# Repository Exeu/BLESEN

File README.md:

# BLESEN
## Bluetooth Low Energy - Sensor 

A simple playground for testing and developing BLE devices.

This Design has a built in 2.4 Ghz 50 Ohm PCB Antennna and is featuring two different sesnsors.

More to come.

## Schematic
[Schematic](BLESEN-Schematic.pdf)

## PCB

## Early prototypes

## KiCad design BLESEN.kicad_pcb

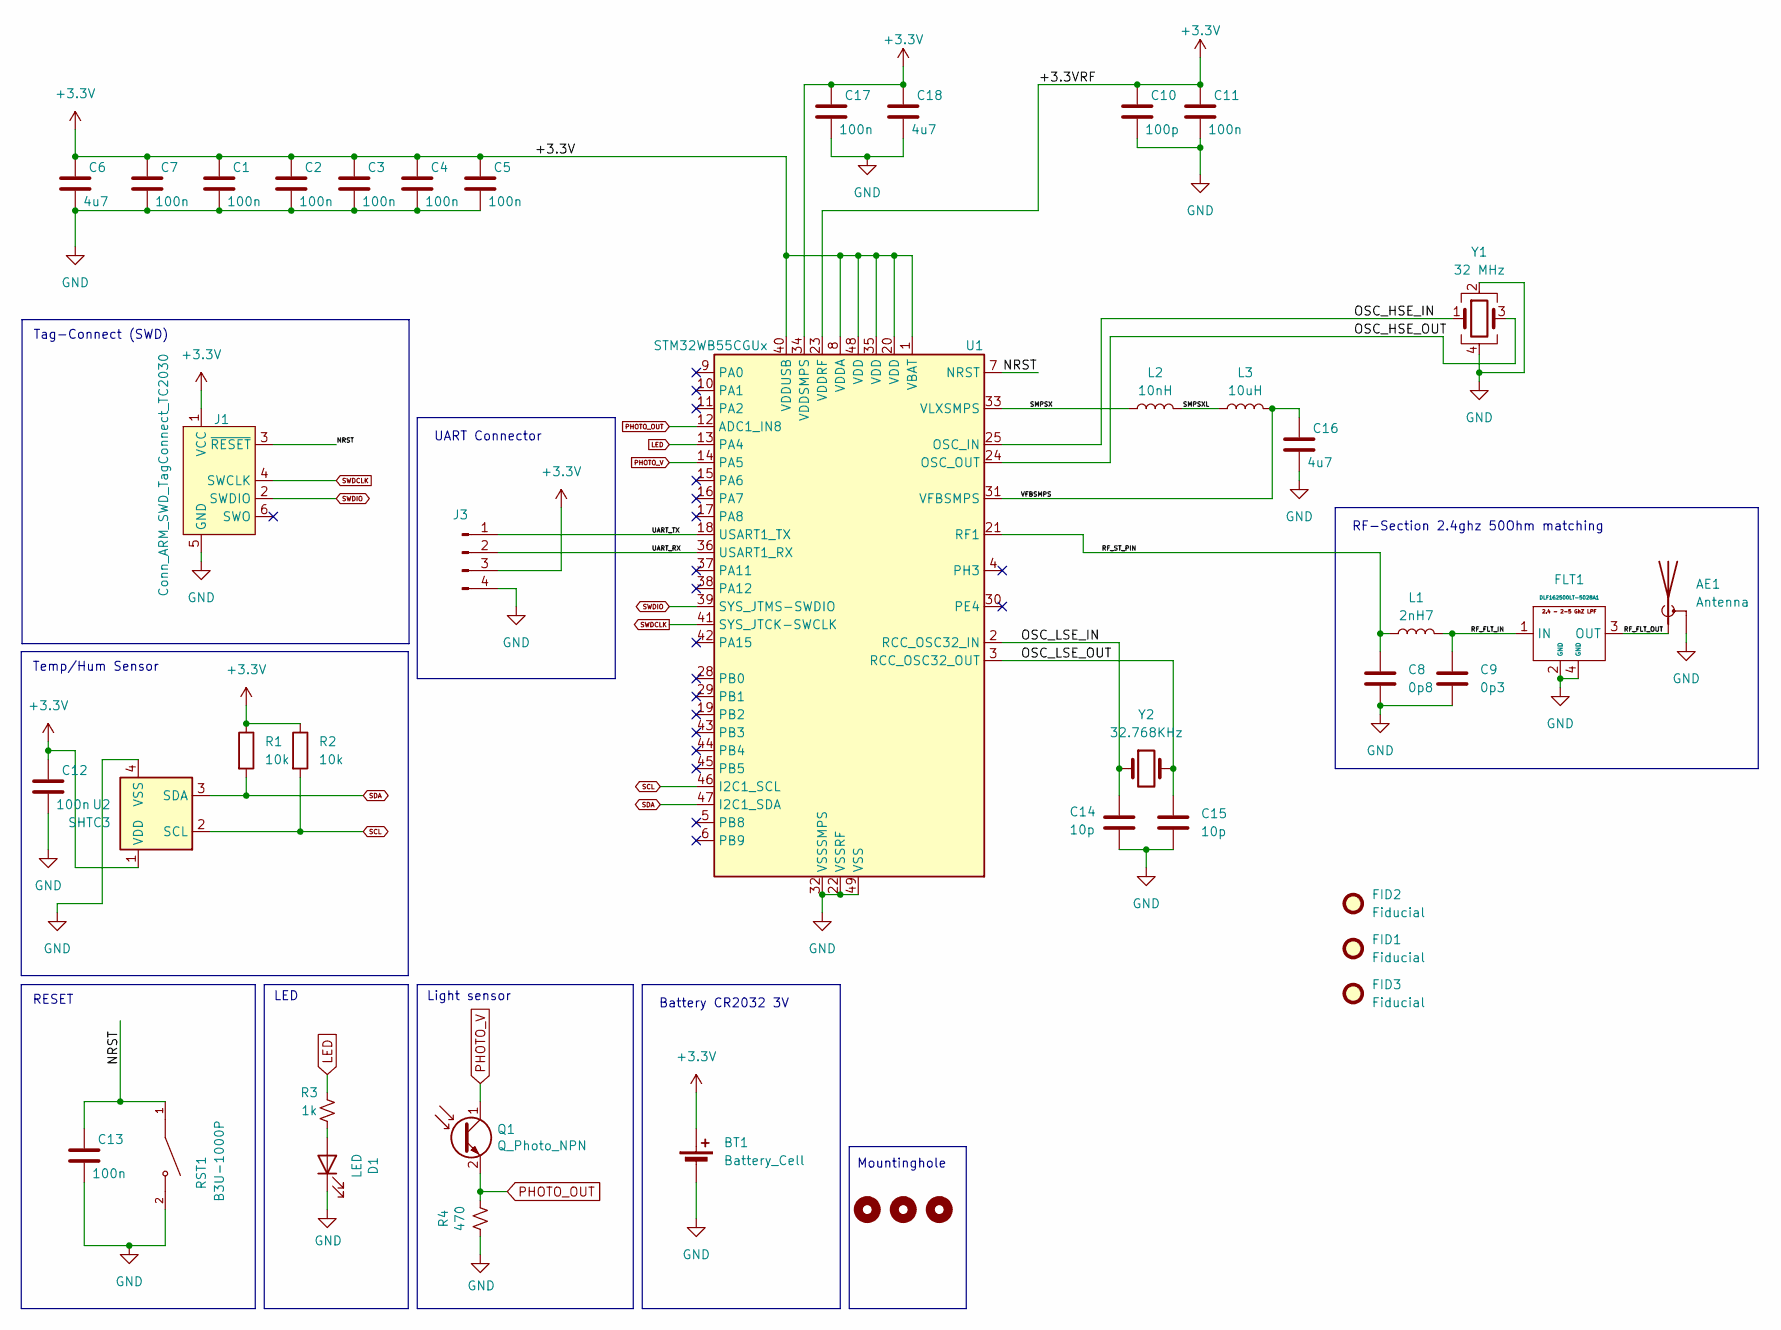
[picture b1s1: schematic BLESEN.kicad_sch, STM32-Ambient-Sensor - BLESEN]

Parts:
AE1: Antenna; Texas_SWRA117D_2.4GHz_Right
BT1: Battery_Cell; BatteryHolder_MPD_BC2003_1x2032
C1, C2, C3, C4, C5, C7, C11, C12, C13, C17: 100n; C_0402_1005Metric; LCSC C1525
C6, C16, C18: 4u7; C_0603_1608Metric; LCSC C19666
C8: 0p8; C_0402_1005Metric; LCSC C327032
C9: 0p3; C_0402_1005Metric; LCSC C76909
C10: 100p; C_0402_1005Metric; LCSC C77177
C14, C15: 10p; C_0402_1005Metric; LCSC C32949
D1: LED; LED_0603_1608Metric; LCSC C2286
FID1, FID2, FID3: Fiducial; Fiducial_0.5mm_Mask1mm
FLT1: DLF162500LT-5028A1; LCSC C531364
H2, H3, H4: MountingHole; MountingHole_2.2mm_M2_DIN965
J1: Conn_ARM_SWD_TagConnect_TC2030; Tag-Connect_TC2030-IDC-NL_2x03_P1.27mm_Vertical
J3: PinHeader_1x04_P2.00mm_Vertical
L1: 2nH7; L_0402_1005Metric; LCSC C434826
L2: 10nH; L_0402_1005Metric; LCSC C464435
L3: 10uH; L_0805_2012Metric; LCSC C98030
Q1: Q_Photo_NPN; D_0603_1608Metric; LCSC C146233
R1, R2: 10k; R_0402_1005Metric; LCSC C25744
R3: 1k; R_0402_1005Metric; LCSC C11702
R4: 470; R_0402_1005Metric; LCSC C25117
RST1: B3U-1000P; SW_SPST_B3U-1000P; LCSC C231329
U1: STM32WB55CGUx; QFN-48-1EP_7x7mm_P0.5mm_EP5.6x5.6mm; LCSC C404023
U2: SHTC3; Sensirion_DFN-4-1EP_2x2mm_P1mm_EP0.7x1.6mm; LCSC C194656
Y1: 32 MHz; Crystal_SMD_2016-4Pin_2.0x1.6mm; LCSC C843260
Y2: 32.768KHz; Crystal_SMD_2012-2Pin_2.0x1.2mm; LCSC C528982

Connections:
+3.3V: BT1.1 (+), C1.1, C2.1, C3.1, C4.1, C5.1, C6.1, C7.1, C10.1, C11.1, C12.1, C17.1, C18.1, J1.1 (VCC), J3.3, R1.1, R2.1, U1.1 (VBAT), U1.8 (VDDA), U1.20 (VDD), U1.23 (VDDRF), U1.34 (VDDSMPS), U1.35 (VDD), U1.40 (VDDUSB), U1.48 (VDD), U2.1 (VDD)
/NRST: C13.1, J1.3 (~RESET), RST1.1, U1.7 (NRST)
/OSC_HSE_IN: U1.25 (OSC_IN), Y1.1
/OSC_HSE_OUT: U1.24 (OSC_OUT), Y1.3
/OSC_LSE_IN: C14.1, U1.2 (RCC_OSC32_IN), Y2.1
/OSC_LSE_OUT: C15.1, U1.3 (RCC_OSC32_OUT), Y2.2
/RF_FLT_IN: C9.1, FLT1.1 (IN), L1.2
/RF_FLT_OUT: AE1.1 (A), FLT1.3 (OUT)
/RF_ST_PIN: C8.1, L1.1, U1.21 (RF1)
/SMPSX: L2.1, U1.33 (VLXSMPS)
/SMPSXL: L2.2, L3.1
/UART_RX: J3.2, U1.36 (USART1_RX)
/UART_TX: J3.1, U1.18 (USART1_TX)
/VFBSMPS: C16.1, L3.2, U1.31 (VFBSMPS)
GND: AE1.2 (Shield), BT1.2 (-), C1.2, C2.2, C3.2, C4.2, C5.2, C6.2, C7.2, C8.2, C9.2, C10.2, C11.2, C12.2, C13.2, C14.2, C15.2, C16.2, C17.2, C18.2, D1.1 (K), FLT1.2 (GND), FLT1.4 (GND), J1.5 (GND), J3.4, R4.1, RST1.2, U1.22 (VSSRF), U1.32 (VSSSMPS), U1.49 (VSS), U2.4 (VSS), Y1.2, Y1.4
LED: R3.2, U1.13 (PA4)
unnamed: D1.2 (A), R3.1
PHOTO_OUT: Q1.2 (E), R4.2, U1.12 (ADC1_IN8)
PHOTO_V: Q1.1 (C), U1.14 (PA5)
SCL: R2.2, U1.46 (I2C1_SCL), U2.2 (SCL)
SDA: R1.2, U1.47 (I2C1_SDA), U2.3 (SDA)
SWDCLK: J1.4 (SWCLK), U1.41 (SYS_JTCK-SWCLK)
SWDIO: J1.2 (SWDIO), U1.39 (SYS_JTMS-SWDIO)

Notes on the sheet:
LED
RESET
Mountinghole
RF-Section 2.4ghz 50Ohm matching
UART Connector
Light sensor
Battery CR2032 3V
Temp/Hum Sensor
Tag-Connect (SWD)

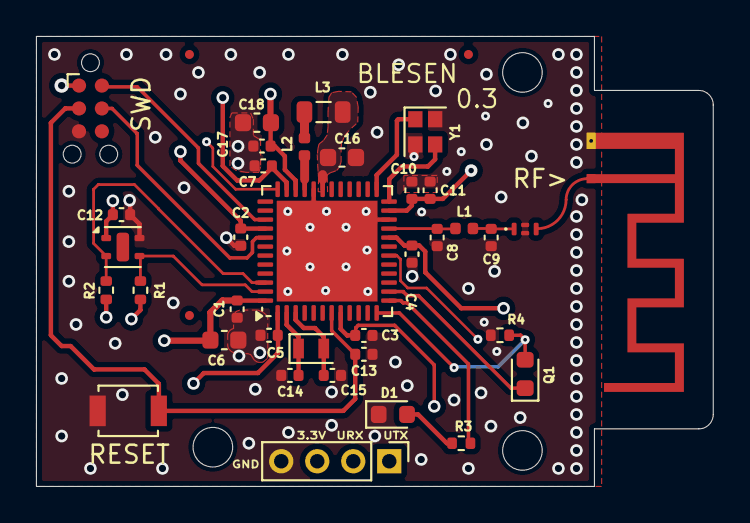
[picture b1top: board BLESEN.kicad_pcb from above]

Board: 4 copper layers, 37.6 x 25.0 mm, 43 parts (1 on the bottom side), 23 nets.

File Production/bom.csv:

Designator,Footprint,Quantity,Value,LCSC Part #
"C1, C11, C12, C13, C17, C2, C3, C4, C5, C7",0402,10,100n,C1525
C10,0402,1,100p,C1546
"C14, C15",0402,2,10p,C32949
"C16, C18, C6",0603,3,4u7,C19666
C8,0402,1,0p8,C327032
C9,0402,1,0p3,C76909
D1,0603,1,LED,C2286
FLT1,DLF162500LT-5028A1,1,DLF162500LT-5028A1,C531364
L1,0402,1,2nH7,C434826
L2,0402,1,10nH,C464435
L3,0805,1,10uH,C98030
Q1,0603,1,Q_Photo_NPN,C146233
"R1, R2",0402,2,10k,C25744
R3,0402,1,1k,C11702
R4,0402,1,470,C25117
RST1,SW_SPST_B3U-1000P,1,B3U-1000P,C231329
U1,QFN-48-1EP_7x7mm_P0.5mm_EP5.6x5.6mm,1,STM32WB55CGUx,C404023
U2,Sensirion_DFN-4_1.5x1.5mm_P0.8mm_SHT4x_NoCentralPad,1,SHT4x,C7461862
Y1,Crystal_SMD_2016-4Pin_2.0x1.6mm,1,32 MHz,C843260
Y2,Crystal_SMD_2012-2Pin_2.0x1.2mm,1,32.768KHz,C528982

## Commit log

2024-06-05 Tweaks
2024-06-05 Add schematic as PDF and PCB overview
2024-07-13 Release 0.4
2024-07-28 Sht4x
2024-09-28 new gerbers
2025-06-20 Drop unused stuff
